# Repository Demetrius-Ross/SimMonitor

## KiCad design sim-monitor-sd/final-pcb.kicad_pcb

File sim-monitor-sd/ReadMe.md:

# ESP32 Circuit Wiring Guide

This document explains how to wire up the ESP32 with a **DC-DC buck converter, optocoupler signals, LEDs, and input components**.

## **1. Power Supply & ESP32 Connections**
| Component | Pin Name | Connected To | Notes |
|-----------|---------|--------------|-------|
| **24V Input** | VIN | MP2315 VIN | Main power source |
| **MP2315 (Buck Converter)** | VOUT | ESP32 **5V Pin** | Provides stable 5V power |
| **MP2315** | GND | Common GND | Ground connection for all components |
| **ESP32** | 3.3V | Various Components | Powers optocouplers, LEDs, and GPIO pull-ups |
| **ESP32** | GND | Common GND | Ground for all components |

---

## **2. Optocoupler (TLP291-4) to ESP32 & External Inputs**
| TLP291-4 Pin | Connected To | ESP32 GPIO | Notes |
|--------------|-------------|------------|-------|
| **Pin 1 (Anode 1)** | External Signal 1 (Ramp Up) | - | Uses **220Ω series resistor** |
| **Pin 2 (Cathode 1)** | GND | - | Completes LED circuit |
| **Pin 3 (Anode 2)** | External Signal 2 (Ramp Down) | - | Uses **220Ω series resistor** |
| **Pin 4 (Cathode 2)** | GND | - | Completes LED circuit |
| **Pin 5 (Anode 3)** | External Signal 3 (Home) | - | Uses **220Ω series resistor** |
| **Pin 6 (Cathode 3)** | GND | - | Completes LED circuit |
| **Pin 9 (Emitter 1)** | GND | - | Shared ground |
| **Pin 10 (Collector 1)** | ESP32 GPIO14 | **Ramp Up Status** |
| **Pin 11 (Emitter 2)** | GND | - | Shared ground |
| **Pin 12 (Collector 2)** | ESP32 GPIO27 | **Ramp Down Status** |
| **Pin 13 (Emitter 3)** | GND | - | Shared ground |
| **Pin 14 (Collector 3)** | ESP32 GPIO26 | **Home Status** |
| **ESP32 GPIOs** | **10kΩ Pull-down Resistor** | **GND** | Ensures stable LOW state |

---

## **3. Status LEDs for Optocoupler Outputs**
| LED Color | LED Anode (+) | LED Cathode (-) | Resistor | Notes |
|-----------|--------------|----------------|---------|------|
| **Red (Ramp Up)** | 3.3V | ESP32 GPIO14 | 470Ω | Turns ON when Ramp Up is active |
| **Green (Ramp Down)** | 3.3V | ESP32 GPIO27 | 470Ω | Turns ON when Ramp Down is active |
| **Blue (Home)** | 3.3V | ESP32 GPIO26 | 470Ω | Turns ON when Home is active |

---

## **4. Capacitors for Power Stability**
| Capacitor | Connected To | Purpose |
|-----------|-------------|---------|
| **22µF 25V** | MP2315 VIN (24V) to GND | Stabilizes DC-DC input |
| **10µF 25V** | MP2315 VOUT (5V) to GND | Stabilizes ESP32 power |
| **0.1µF 10V x2** | ESP32 3.3V rail to GND | Reduces high-frequency noise |

---

## **Final Notes**
- **Ensure correct polarity** for power input components.
- **Mount capacitors close to the MP2315 regulator** for best stability.
- **Use 10kΩ pull-downs for stable ESP32 GPIO readings.**

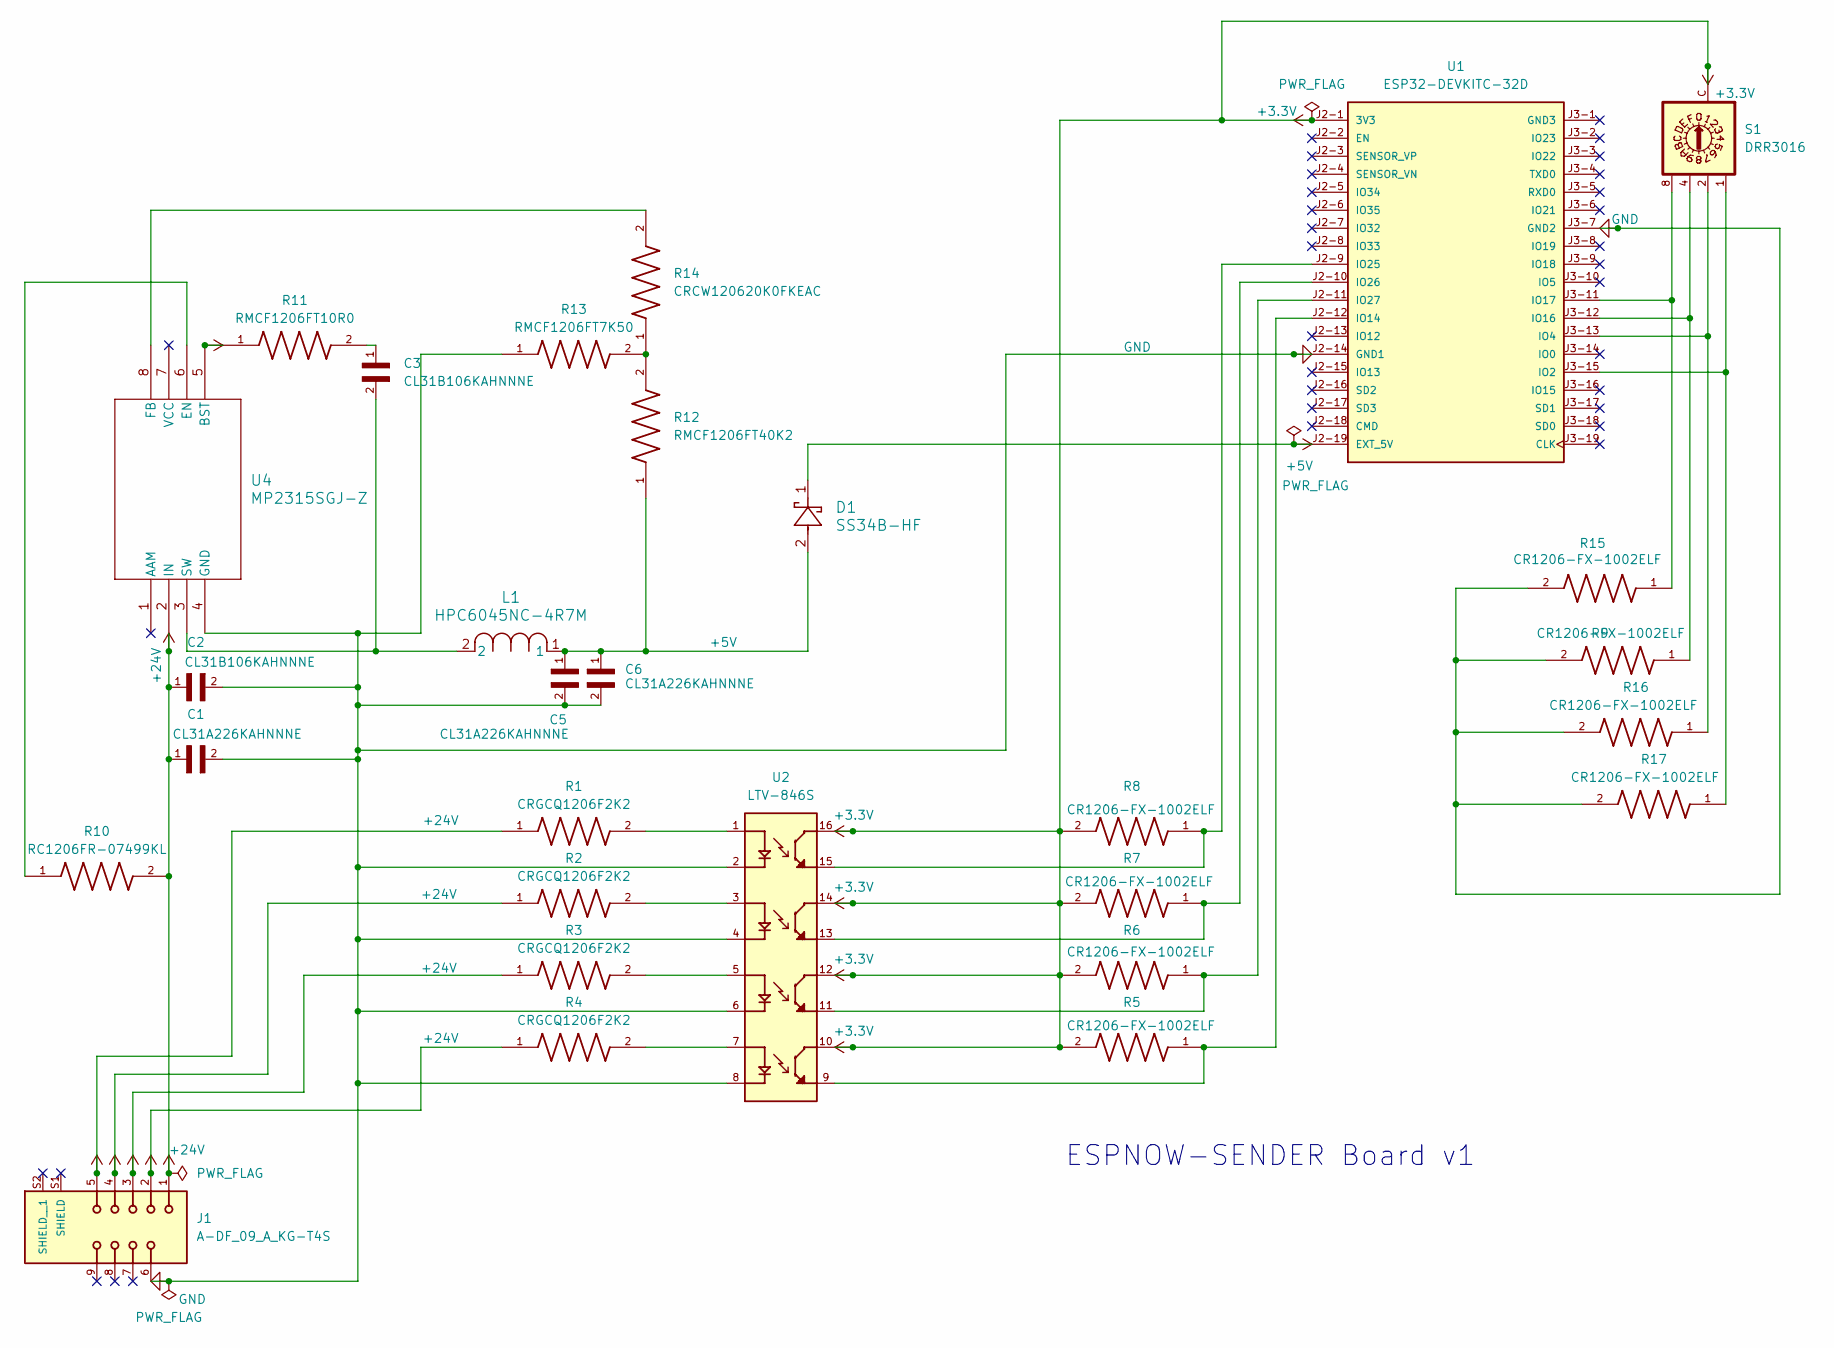
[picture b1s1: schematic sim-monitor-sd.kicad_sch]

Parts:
C1, C5, C6: CL31A226KAHNNNE; CAPC3216X180N
C2, C3: CL31B106KAHNNNE; CAPC3216X180N
D1: SS34B-HF; DO214AASMB_CIP
J1: A-DF_09_A_KG-T4S; ASSMANN_A-DF_09_A_KG-T4S; PARTREV 05
L1: HPC6045NC-4R7M; IND_HPC6045NC_TTA
R1, R2, R3, R4: CRGCQ1206F2K2; RESC3115X65N
R5, R6, R7, R8, R9, R15, R16, R17: CR1206-FX-1002ELF; RESC3216X75N
R10: RC1206FR-07499KL; RESC3116X65N
R11: RMCF1206FT10R0; RESC3216X70N
R12: RMCF1206FT40K2; RESC3216X70N
R13: RMCF1206FT7K50; RESC3216X70N
R14: CRCW120620K0FKEAC; RESC3015X65N
S1: DRR3016; DRR3010; MPN DRR3016
U1: ESP32-DEVKITC-32D; MODULE_ESP32-DEVKITC-32D; PARTREV V4
U2: LTV-846S; SOIC254P1016X460-16N; PARTREV H
U4: MP2315SGJ-Z; TSOT23-8_MP2315S_MNP

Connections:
+3.3V: R5.2, R6.2, R7.2, R8.2, S1.C, U1.J2-1 (3V3), U2.10, U2.12, U2.14, U2.16
+5V: D1.1, R11.1, U1.J2-19 (EXT_5V), U4.5 (BST)
+24V: C1.1, C2.1, J1.1, J1.2, J1.3, J1.4, J1.5, R1.1, R2.1, R3.1, R4.1, R10.2, U4.2 (IN)
GND: C1.2, C2.2, C5.2, C6.2, J1.6, R9.2, R13.1, R15.2, R16.2, R17.2, U1.J2-14 (GND1), U1.J3-7 (GND2), U2.2, U2.4, U2.6, U2.8, U4.4 (GND)
unnamed: C3.1, R11.2
unnamed: C5.1, C6.1, D1.2, L1.1, R12.1
unnamed: R1.2, U2.1
unnamed: R2.2, U2.3
unnamed: R3.2, U2.5
unnamed: R4.2, U2.7
unnamed: R12.2, R13.2, R14.1
unnamed: R17.1, S1.1, U1.J3-15 (IO2)
unnamed: R16.1, S1.2, U1.J3-13 (IO4)
unnamed: R5.1, U1.J2-12 (IO14), U2.9
unnamed: R15.1, S1.4, U1.J3-12 (IO16)
unnamed: R9.1, S1.8, U1.J3-11 (IO17)
unnamed: R8.1, U1.J2-9 (IO25), U2.15
unnamed: R7.1, U1.J2-10 (IO26), U2.13
unnamed: R6.1, U1.J2-11 (IO27), U2.11
unnamed: R10.1, U4.6 (EN)
unnamed: R14.2, U4.8 (FB)
unnamed: C3.2, L1.2, U4.3 (SW)

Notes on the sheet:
ESPNOW-SENDER Board v1

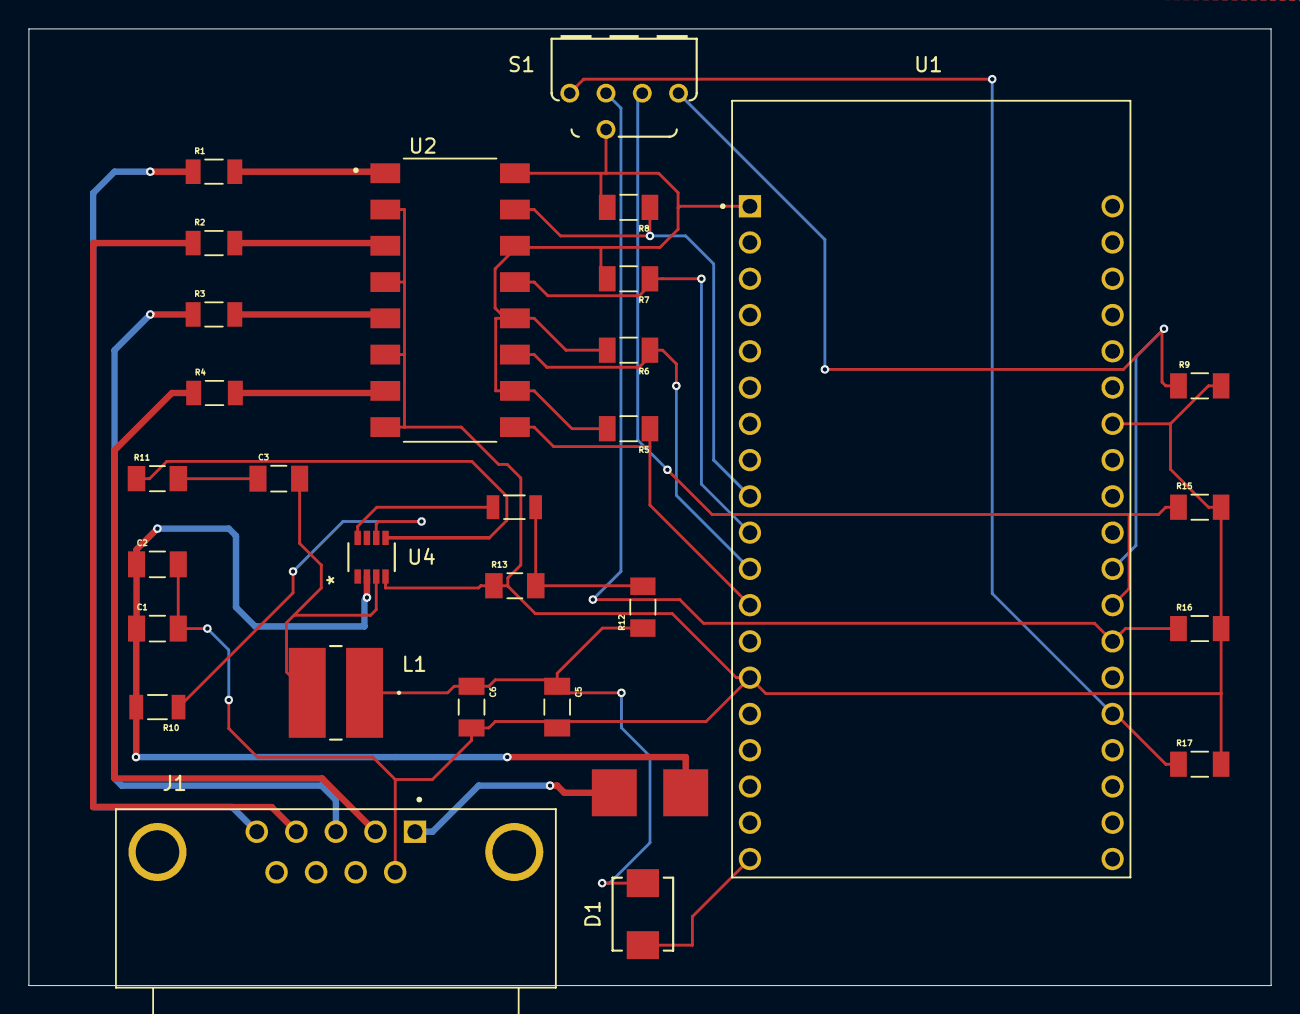
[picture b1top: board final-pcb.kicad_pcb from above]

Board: 2 copper layers, 87.0 x 67.0 mm, 29 parts (0 on the bottom side), 22 nets.

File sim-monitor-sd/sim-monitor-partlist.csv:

Reference,Qty,Serial Number,Name,Value,Price Per,Price Total
"C1,C5,C6",3,CL31A226KAHNNNE,Ceramic Capacitor,22  µF,$0.26 ,$0.78 
"C2,C3",2,CL31B106KAHNNNE,Ceramic Capacitor,10 µF,$0.11 ,$0.22 
D1,1,SS34B-HF,Schottky Diode,40V @ 3A,$0.27 ,$0.27 
J1,1,A-DF 09 A/KG-T4S,D-SUB ,,$0.77 ,$0.77 
L1,1,HPC6045NC-4R7M,Shielded Wirewound Inductor,4.7 µH,$0.11 ,$0.11 
"R1,R2,R3,R4",4,CRGCQ1206F2K2,Chip Resistor 1206,2.2 kOhms,$0.10 ,$0.40 
"R5,R6,R7,R8,R9,R15,R16,R17",8,CR1206-FX-1002ELF,Chip Resistor 1206,10 kOhms,$0.10 ,$0.80 
R10,1,RC1206FR-07499KL,Chip Resistor 1206,499 kOhms,$0.10 ,$0.10 
R11,1,RMCF1206FT10R0,Chip Resistor 1206,10 Ohms,$0.10 ,$0.10 
R12,1,RMCF1206FT40K2,Chip Resistor 1206,40.2 kOhms,$0.10 ,$0.10 
R13,1,RMCF1206FT7K50,Chip Resistor 1206,7.5 kOhms,$0.10 ,$0.10 
R14,1,CRCW120620K0FKEAC,Chip Resistor 1206,20 kOhms,$0.10 ,$0.10 
S1,1,DRR3016,Rot Switch,16 Pos Hex,$3.09 ,$3.09 
U1,1,ESP32-DEVKITC-32D,ESP32,,,
U2,1,LTV-846S,Optocoupler,4-Channel,$1.07 ,$1.07 
U4,1,MP2315SGJ-Z,Buck Converter,,$2.92 ,$2.92 
,1,RA111C1021-116,On-Off Switch,,$1.57 ,$1.57 
,,,,,,
,,,,,,
,,,,,,
,,,,,,
,,,,,,
,,,,,,Total
,,,,,,$12.50
